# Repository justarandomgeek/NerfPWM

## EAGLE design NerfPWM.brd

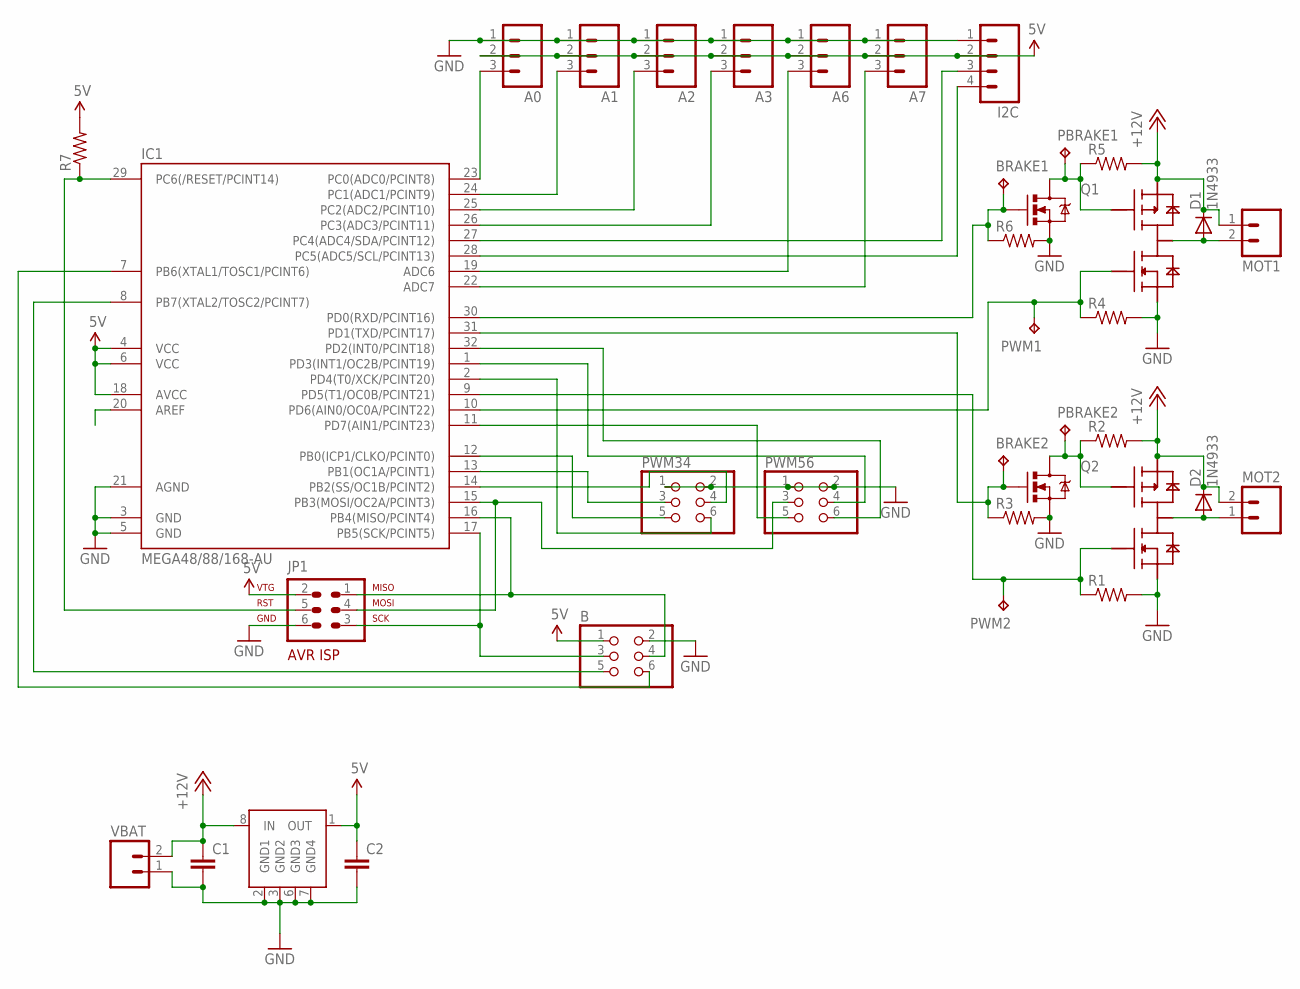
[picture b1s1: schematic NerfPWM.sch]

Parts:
A0, A1, A2, A3, A6, A7: M03PTH; 1X03
B: PINHD-2X3; 2X03
BRAKE1, BRAKE2: TPTP10R; TP10R
C1, C2: CAP1206; 1206
D1, D2: 1N4933; DO41-10
I2C: M04PTH; 1X04
IC1: MEGA48/88/168-AU; TQFP32-08
JP1: AVR-ISP-6
MOT1, MOT2: M023.5MM_LOCK; SCREWTERMINAL-3.5MM-2_LOCK
PBRAKE1, PBRAKE2: TPTP10R; TP10R
PWM1, PWM2: TPTP10R; TP10R
PWM34, PWM56: PINHD-2X3; 2X03
Q1, Q2: MOSFET-NCHANNELSMD; SOT23-3
R1, R2, R3, R4, R5, R6, R7: RESISTOR; 0805
U$3: MC78L00AD; SOIC8
U$4, U$5: SI4501BDY; SOIC8
VBAT: M023.5MM_LOCK; SCREWTERMINAL-3.5MM-2_LOCK

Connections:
5V: A0.2, A1.2, A2.2, A3.2, A6.2, A7.2, B.1, C2.1, I2C.2, IC1.4 (VCC), IC1.6 (VCC), IC1.18 (AVCC), JP1.2, R7.2, U$3.1 (OUT)
+12V: C1.1, D1.C, D2.C, MOT1.1, MOT2.2, R2.2, R5.2, U$3.8 (IN), U$4.3 (S2), U$5.3 (S2), VBAT.2
A1: A1.3, IC1.24 (PC1(ADC1/PCINT9))
A2: A2.3, IC1.25 (PC2(ADC2/PCINT10))
A3: A3.3, IC1.26 (PC3(ADC3/PCINT11))
A6: A6.3, IC1.19 (ADC6)
A7: A7.3, IC1.22 (ADC7)
A): A0.3, IC1.23 (PC0(ADC0/PCINT8))
B4: B.4, IC1.16 (PB4(MISO/PCINT4)), JP1.1
B5: B.3, IC1.17 (PB5(SCK/PCINT5)), JP1.3
B6: B.6, IC1.7 (PB6(XTAL1/TOSC1/PCINT6))
B7: B.5, IC1.8 (PB7(XTAL2/TOSC2/PCINT7))
BRAKE1: BRAKE1.TP, IC1.30 (PD0(RXD/PCINT16)), Q1.1 (G), R6.1
BRAKE2: BRAKE2.TP, IC1.31 (PD1(TXD/PCINT17)), Q2.1 (G), R3.1
BRAKE3: IC1.12 (PB0(ICP1/CLKO/PCINT0)), PWM34.5
BRAKE4: IC1.2 (PD4(T0/XCK/PCINT20)), PWM34.6
BRAKE5: IC1.11 (PD7(AIN1/PCINT23)), PWM56.5
BRAKE6: IC1.32 (PD2(INT0/PCINT18)), PWM56.6
GND: A0.1, A1.1, A2.1, A3.1, A6.1, A7.1, B.2, C1.2, C2.2, I2C.1, IC1.3 (GND), IC1.5 (GND), IC1.21 (AGND), JP1.6, PWM34.1, PWM34.2, PWM56.1, PWM56.2, Q1.2 (S), Q2.2 (S), R1.2, R3.2, R4.2, R6.2, U$3.2 (GND1), U$3.3 (GND2), U$3.6 (GND3), U$3.7 (GND4), U$4.1 (S1), U$5.1 (S1), VBAT.1
unnamed: PBRAKE2.TP, Q2.3 (D), R2.1, U$5.4 (G2)
unnamed: PBRAKE1.TP, Q1.3 (D), R5.1, U$4.4 (G2)
PWM1: IC1.10 (PD6(AIN0/OC0A/PCINT22)), PWM1.TP, R4.1, U$4.2 (G1)
PWM2: IC1.9 (PD5(T1/OC0B/PCINT21)), PWM2.TP, R1.1, U$5.2 (G1)
PWM3: IC1.13 (PB1(OC1A/PCINT1)), PWM34.3
PWM4: IC1.14 (PB2(SS/OC1B/PCINT2)), PWM34.4
PWM5: IC1.15 (PB3(MOSI/OC2A/PCINT3)), JP1.4, PWM56.3
PWM6: IC1.1 (PD3(INT1/OC2B/PCINT19)), PWM56.4
RESET: IC1.29 (PC6(/RESET/PCINT14)), JP1.5, R7.1
SCL: I2C.4, IC1.28 (PC5(ADC5/SCL/PCINT13))
SDA: I2C.3, IC1.27 (PC4(ADC4/SDA/PCINT12))
VMOT1: D1.A, MOT1.2, U$4.5 (D), U$4.6 (D), U$4.7 (D), U$4.8 (D)
VMOT2: D2.A, MOT2.1, U$5.5 (D), U$5.6 (D), U$5.7 (D), U$5.8 (D)

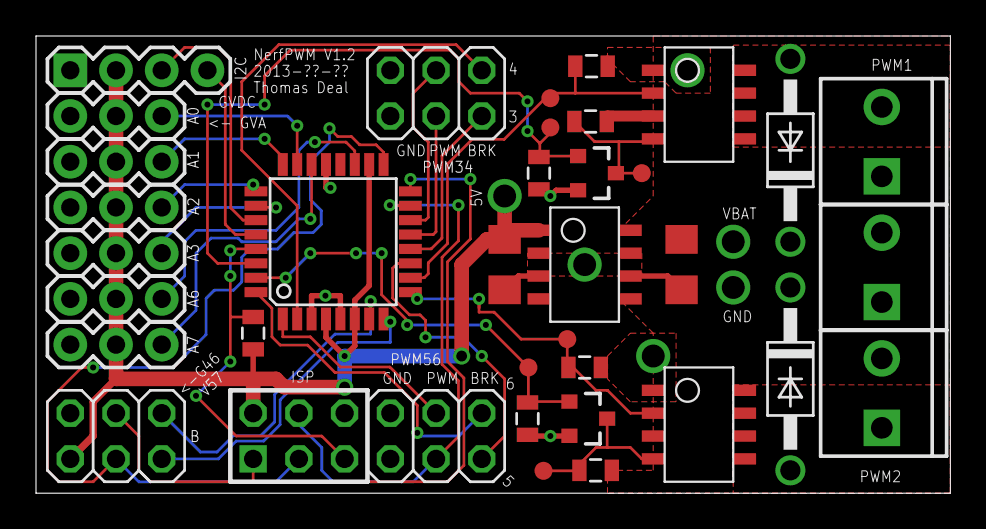
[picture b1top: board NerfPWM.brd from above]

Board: 2 copper layers, 50.8 x 25.4 mm, 37 parts (0 on the bottom side), 32 nets.

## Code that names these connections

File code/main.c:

/* ========================================================================== */
/*                                                                            */
/*   main.c                                                                   */
/*   (c) 2011 Thomas Deal                                                     */
/*                                                                            */
/*   Description                                                              */
/*                                                                            */
/* ========================================================================== */

#include <avr/power.h>
#include "nerfpwm.h"
#include "mixer.h"
#include "adc.h"
#include "pwm.h"

/*

tasks:

* read adc - in adc.c	
* I2C add-ons
* 	-ISR: receive packets, send packet, set flag (or callback?) on receive (or complete?)
* 	-flags:
* 	-data: 
* 		-out: malloc'd packets
* 		-in: myaddr:7|X:1

ISRs:

INT0_vect			# pin shared with BRAKE6 #
INT1_vect			# pin shared with PWM6 #
PCINT0_vect		# bits 4-7 may be usable / GPIO_B #
PCINT1_vect		# bits 0-3 usable if not used for analog in  #
PCINT2_vect		# some pins usable if not used for PWM/BRAKE #
WDT_vect			unused ? maybe use for threading ?
TIMER2_COMPA_vect	unused # timing forced for hardware PWM for PWM5 if used #
TIMER2_COMPB_vect	unused # timing forced for hardware PWM for PWM6 if used #
TIMER2_OVF_vect	unused # timing forced for hardware PWM for PWM5/6 if used #
TIMER1_CAPT_vect	unused # timing range forced by PWM for PWM3/4 if used #
TIMER1_COMPA_vect	unused # timing forced for hardware PWM for PWM3 if used #
TIMER1_COMPB_vect	unused # timing forced for hardware PWM for PWM4 if used #
TIMER1_OVF_vect	unused # timing forced for hardware PWM for PWM3/4 if used #
TIMER0_COMPA_vect   unused # timing forced for hardware PWM for PWM1 #
TIMER0_COMPB_vect	unused # timing forced for hardware PWM for PWM2 #
TIMER0_OVF_vect	unused # timing forced for hardware PWM for PWM1/2 #
SPI_STC_vect		# pins used by PWM4/5, GPIO #
USART_RX_vect		# pins used as BRAKE1/2 #
USART_URDE_vect	# pins used as BRAKE1/2 #
USART_TX_vect		# pins used as BRAKE1/2 #
ADC_vect			used for reading inputs
EE_READY_vect		unused
ANALOG_COMP_vect	# not usable, pins are used for PWM1/BRAKE5 #
TWI_vect			used for packet net of peripherals
SPM_REDY_vect		unused
*/

#include <util/delay.h>

int main(void)
{
	// in case CLK_DIV_8 is programmed
	clock_prescale_set(clock_div_1);
	
	settings_init();
	
	//init_twi();
	
	adc_init();
	pwm_init();
		
	
	sei();
		
	
	while(1){
		if(adc_new_data)
		{
			adc_new_data=0;
			
			// calculate new mix values.
			for(int i=0;i<MAX_MIXERS;i++) apply_mix(&settings.mixData[i]);
		
			// copy output values from mixOuts to appropriate places...
			pwm_write(&mixOuts[OUT_PWM1]);	
			
			// update previous values for edge detectors
			for(int i=0;i<MAX_EDGES;i++) edgePrev[i] = read_digital(settings.edgeData[i]);
 								
			_delay_ms(5);	
		}
		
	}
}

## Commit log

2013-07-13 Import existing Schematic/Board files.
2013-07-28 Changed ISP header.
2013-07-28 Added code. Updated .gitignore to reflect program ignores.
2013-08-01 Increased spacing between high-power traces/pours. Enabled thermals for vias (specifically, for the large vias providing power/ground for hacking).
2013-08-02 Increased text size to improve silkscreen readability, and rearranged as needed to fit. Changed version number/date to unspecified until next tagged release.
2013-08-04 Increased spacing around FET ground connections.
2013-08-04 Lots more code.
2013-08-04 Changed PWM 1/2 writing to a macro. This will make it easier to apply the same code for PWMs 3-6.
    Converted mix source/dest/multiplex values to be enum types.
2013-08-04 enum for switches (logic, to be renamed soon...) clean up macros from last commit a little.
2013-08-19 Makefile: MCU switched to 328 for prototype boards. Also added targets flash/eeprom, and configured debug/programmer options adc.c: adc_val is now volatile. Also, cleaned up some of the init/ISR code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
    main.c: added initializer and macro for default eeprom settings. Removed clock speed config options, this will only run from on-chip 8MHz for now. Now reads eeprom settings into ram. Various bugfixes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
2013-08-19 add an ignore for __avr_gdbinit.
2013-08-19 Clean up some cases with A...B syntax.
2013-08-24 lots of code reorg.
2013-08-25 more reorg, also made many functions static.
2013-08-25 move settings to a seperate header. ADC now configures pins based on settings. PWM configures pins on the pwm34 header.
2013-08-25 minor changes to pinmap.txt, moved to code dir.
2013-08-29 lots of settings, more reorg, and a dependancy chart generator.
2013-09-08 Added support for constants in mixer. Use Offset as constant value, when added it will wrap correctly. Added settings configuration for my RapidStrike with first prototype board installed.
2013-09-09 Some minor changes to PWM module. Braking still does not work as expected. Changes to settings config for my RS.
2013-09-28 Silkscreen tag Mainboard V1.1 for ordering new boards.
2013-10-20 Board revisions for easier assembly of next batch.
2014-01-18 Makefile switched to atmega168 default, for more recent boards. Added profile for Stryfe.
2014-01-18 main.c: Added a 10ms delay after updating mixes. This reduces glitches in fast-changing outputs. mixer.h: corrected numbering is comment. pwm.c: correctly turn off PWM pin when value is 0.
2014-01-25 Updated/working Stryfe profile.
2014-02-09 Better named settings enums.
    * Analog Out enum is now OUT_*
    * Multiplex enum is now MP_*
    * Logic functions now have an enum instead of having hard-coded constants. They are OP_*. OP_AC_* use one analog and one constant, OP_AA_* use two analogs, and OP_DD_* use two digitals.
2014-02-11 Mixer updates to add Edge Detectors, and other minor changes.
    * Add edge-detectors as switch types.
    * mixOuts is now sized by NUM_MIXOUTS, which is the last value in the enum.
    * Named vars OUT_VAR1-4.
2014-04-18 partial work on RS burst mode.
2016-01-22 Add default safe settings if no PROFILE is set. Tweak RAPIDSTRIKE PWM levels.
2017-03-30 Old uncommitted changes

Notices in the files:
parts and their libraries:
SparkFun: Licensing: CC v3.0 Share-Alike You are welcome to use this library for commercial purposes.
